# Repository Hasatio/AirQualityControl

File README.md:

# Air Quality Control

The circuit taken as an example while designing the board [Sparkfun BME688](https://www.sparkfun.com/products/19096)

## Revision 0

### Added:

- 1x TCA9406 (Voltage Level Translator)
- 1x PCA9554 (I/O Expander)
- 8x Relay
- 1x K7805-2000R3L or K7805-2000R3 for 5V supply

### Changed:

- Logo

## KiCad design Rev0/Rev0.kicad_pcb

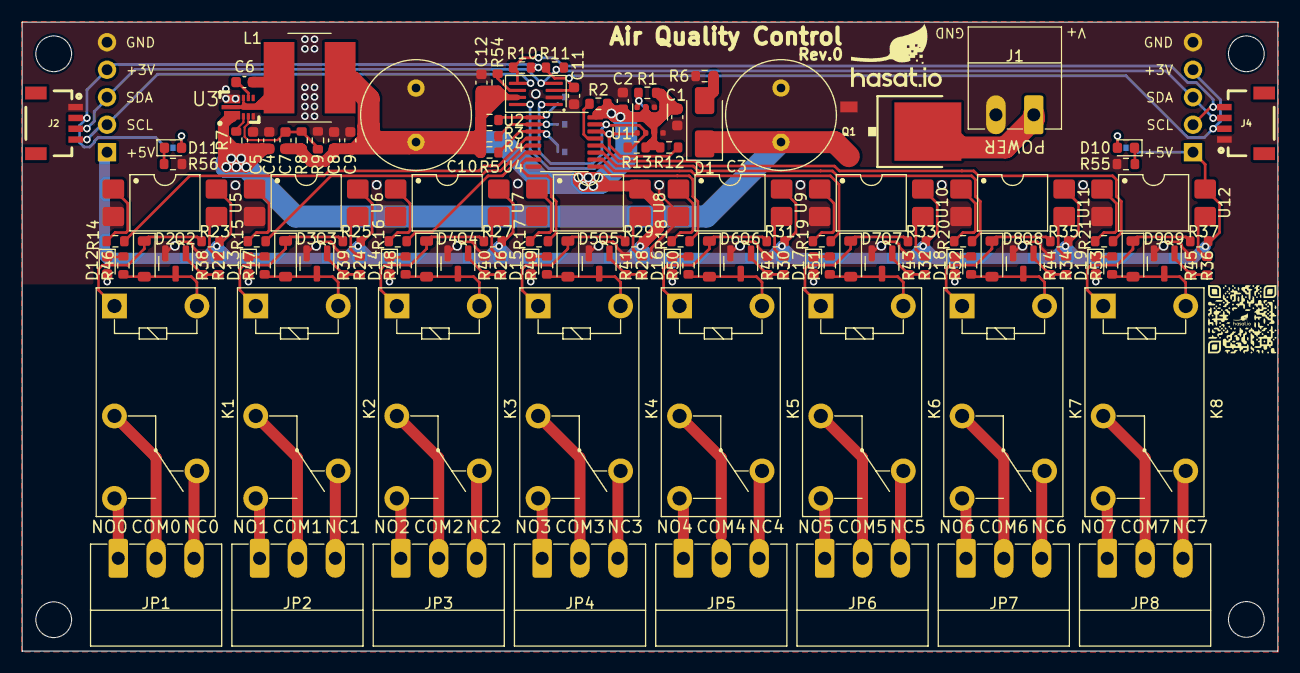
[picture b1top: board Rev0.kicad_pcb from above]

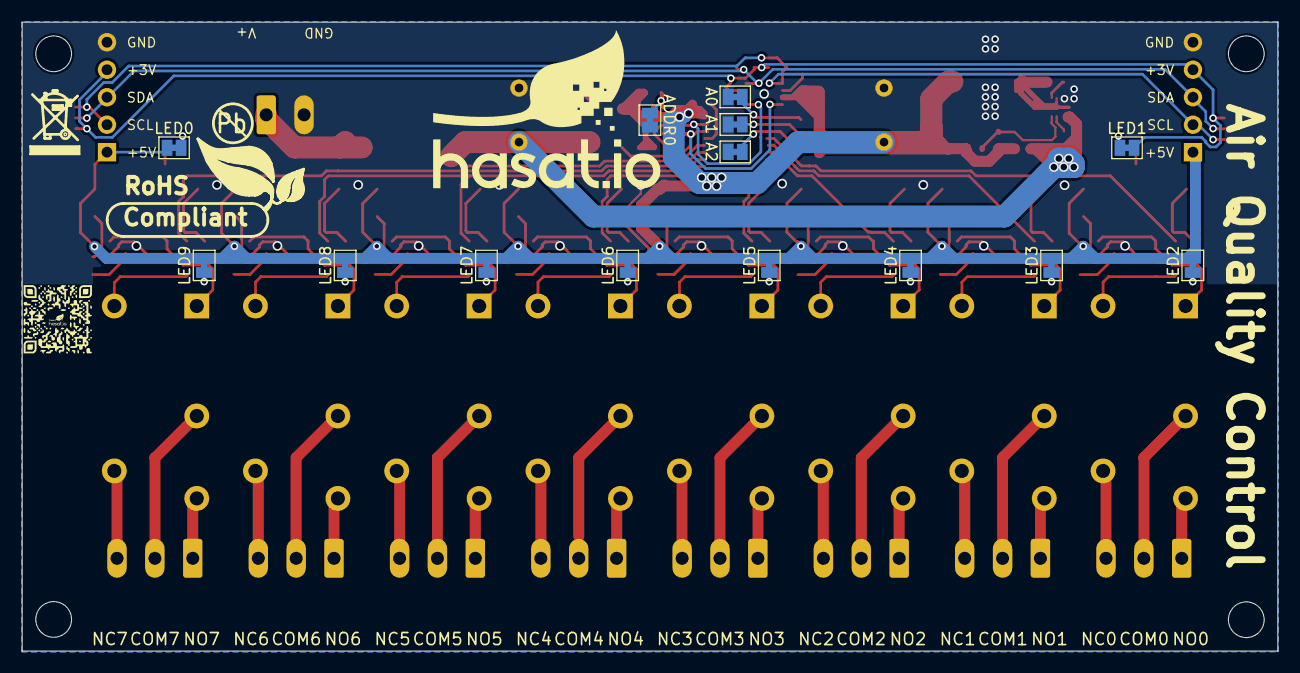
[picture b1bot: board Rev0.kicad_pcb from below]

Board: 2 copper layers, 116.0 x 58.1 mm, 147 parts (17 on the bottom side), 112 nets.

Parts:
A0, A1, A2: SolderJumper_2_Bridged; SolderJumper-2_P1.3mm_Bridged_Pad1.0x1.5mm
ADDR0: SolderJumper_2_Bridged; SolderJumper-2_P1.3mm_Bridged_Pad1.0x1.5mm
C1, C2, C6, C11, C12: 0.1uF; C_0603_1608Metric
C3, C10: 1000uF/35v; C_Radial_D10.0mm_H20.0mm_P5.00mm
C4, C5: 4.7uF-50V; C_0603_1608Metric
C7: 47pF-5%-X7R; C_0603_1608Metric
C8, C9: 22uF; C_0603_1608Metric
D1: Z1SMA4740; D_SMA
D2, D3, D4, D5, D6, D7, D8, D9: 1N4148W; D_SOD-123
D10: GREEN; LED_0603_1608Metric
D11: RED; LED_0603_1608Metric
D12, D13, D14, D15, D16, D17, D18, D19: BLUE; LED_0603_1608Metric
J1: TERMBLOCK_1X2; PhoenixContact_MC_1,5_2-G-3.5_1x02_P3.50mm_Horizontal
J2, J4: QWIIC_RIGHT_ANGLE; 1X04_1MM_RA_STRESSRELIEF
J3, J5: Conn_01x05; PinHeader_1x05_P2.54mm_Vertical
JP1, JP2, JP3, JP4, JP5, JP6, JP7, JP8: HEADER-1X3_508TERM; PhoenixContact_MC_1,5_3-G-3.5_1x03_P3.50mm_Horizontal
K1, K2, K3, K4, K5, K6, K7, K8: G5Q-1; Relay_SPDT_Omron-G5Q-1
L1: 6.8uH; L_Bourns_SRN8040TA
LED0, LED1, LED2, LED3, LED4, LED5, LED6, LED7, LED8, LED9: SolderJumper_2_Bridged; SolderJumper-2_P1.3mm_Bridged_Pad1.0x1.5mm
Q1: AOD417; TO252
Q2, Q3, Q4, Q5, Q6, Q7, Q8, Q9: MMBT2222; SOT-23
R1, R2, R3, R4, R5, R10, R11, R12, R13, R38, R39, R40, R41, R42, R43, R44, R45, R54: 10K; R_0603_1608Metric
R6: 100k; R_0603_1608Metric
R7: 10k; R_0603_1608Metric
R8: 158k; R_0603_1608Metric
R9: 30k; R_0603_1608Metric
R14, R15, R16, R17, R18, R19, R20, R21: 360R; R_0603_1608Metric
R22, R24, R26, R28, R30, R32, R34, R36: 330R; R_0603_1608Metric
R23, R25, R27, R29, R31, R33, R35, R37: 10R; R_0603_1608Metric
R46, R47, R48, R49, R50, R51, R52, R53: 1K; R_0603_1608Metric
R55: 2k2; R_0603_1608Metric
R56: 1k; R_0603_1608Metric
Sign-RecyclBin: LOGO_RECYCLEBIN_1
Sign_Pb-Free: LOGO_PBFREE
Sign_RoHS: Val**; LOGO_ROHS_1
U1: BME688; Bosch_LGA-8_3x3mm_P0.8mm_ClockwisePinNumbering
U2: TCA9406DC; SSOP-8_2.95x2.8mm_P0.65mm
U3: AP63357; V-DFN3020-13
U4: TCA9534A; TSSOP-16_4.4x5mm_P0.65mm
U5, U6, U7, U8, U9, U10, U11, U12: LTV-817S; SMDIP-4_W9.53mm

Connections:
+3.3V: C11.1, J2.2, J3.4, J4.2, J5.4, LED1.1 (A), R10.1, R11.1, U2.3 (VCCA)
+5V: C1.1, C2.1, C7.1, C8.1, C9.1, C10.1, C12.1, J3.1, J5.1, L1.2, LED0.1 (A), LED2.1 (A), LED3.1 (A), LED4.1 (A), LED5.1 (A), LED6.1 (A), LED7.1 (A), LED8.1 (A), LED9.1 (A), R1.2, R2.2, R3.2, R4.2, R5.2, R8.2, R12.1, R13.1, R23.1, R25.1, R27.1, R29.1, R31.1, R33.1, R35.1, R37.1, R54.1, U1.2 (CSB), U1.6 (VDDIO), U1.8 (VDD), U2.7 (VCCB), U4.16 (VDD), U5.4, U6.4, U7.4, U8.4, U9.4, U10.4, U11.4, U12.4
/A0: A0.1 (A), R3.1, U4.1 (A0)
/A1: A1.1 (A), R4.1, U4.2 (A1)
/A2: A2.1 (A), R5.1, U4.3 (A2)
/COM0: JP1.2, K1.2
/COM1: JP2.2, K2.2
/COM2: JP3.2, K3.2
/COM3: JP4.2, K4.2
/COM4: JP5.2, K5.2
/COM5: JP6.2, K6.2
/COM6: JP7.2, K7.2
/COM7: JP8.2, K8.2
/NC0: JP1.3, K1.4
/NC1: JP2.3, K2.4
/NC2: JP3.3, K3.4
/NC3: JP4.3, K4.4
/NC4: JP5.3, K5.4
/NC5: JP6.3, K6.4
/NC6: JP7.3, K7.4
/NC7: JP8.3, K8.4
/NO0: JP1.1, K1.3
/NO1: JP2.1, K2.3
/NO2: JP3.1, K3.3
/NO3: JP4.1, K4.3
/NO4: JP5.1, K5.3
/NO5: JP6.1, K6.3
/NO6: JP7.1, K7.3
/NO7: JP8.1, K8.3
/Out0: R14.2, U4.4 (P0)
/Out1: R15.2, U4.5 (P1)
/Out2: R16.2, U4.6 (P2)
/Out3: R17.2, U4.7 (P3)
/Out4: R18.2, U4.9 (P4)
/Out5: R19.2, U4.10 (P5)
/Out6: R20.2, U4.11 (P6)
/Out7: R21.2, U4.12 (P7)
/Relay0: R22.2, U5.3
/Relay1: R24.1, U6.3
/Relay2: R26.1, U7.3
/Relay3: R28.1, U8.3
/Relay4: R30.1, U9.3
/Relay5: R32.1, U10.3
/Relay6: R34.1, U11.3
/Relay7: R36.1, U12.3
/SCL_A: J2.4, J3.2, J4.4, J5.2, R10.2, U2.5 (SCL_A)
/SCL_B: R12.2, U1.4 (SCK), U2.8 (SCL_B), U4.14 (SCL)
/SDA_A: J2.3, J3.3, J4.3, J5.3, R11.2, U2.4 (SDA_A)
/SDA_B: R13.2, U1.3 (SDI), U2.1 (SDA_B), U4.15 (SDA)
/SDO: ADDR0.1 (A), R1.1, U1.5 (SDO)
GND: A0.2 (B), A1.2 (B), A2.2 (B), ADDR0.2 (B), C1.2, C2.2, C3.2, C4.2, C5.2, C8.2, C9.2, C10.2, C11.2, C12.2, J1.2, J2.1, J3.5, J4.1, J5.5, Q1.1 (G), Q2.2 (E), Q3.2 (E), Q4.2 (E), Q5.2 (E), Q6.2 (E), Q7.2 (E), Q8.2 (E), Q9.2 (E), R6.1, R9.1, R38.1, R39.1, R40.1, R41.1, R42.1, R43.1, R44.1, R45.1, R55.2, R56.2, U1.1 (GND), U1.7 (GND), U2.2 (GND), U3.P$4 (COMP), U3.P$8 (GND), U4.8 (GND), U5.2, U6.2, U7.2, U8.2, U9.2, U10.2, U11.2, U12.2
unnamed: C6.2, L1.1, U3.P$7 (SW), U3.P$9 (SW)
unnamed: D1.2 (A), R6.2
unnamed: D2.2 (A), K1.5, Q2.3 (C), R46.1
unnamed: D2.1 (K), K1.1, R23.2
unnamed: D3.2 (A), K2.5, Q3.3 (C), R47.1
unnamed: D3.1 (K), K2.1, R25.2
unnamed: D4.2 (A), K3.5, Q4.3 (C), R48.1
unnamed: D4.1 (K), K3.1, R27.2
unnamed: D5.2 (A), K4.5, Q5.3 (C), R49.1
unnamed: D5.1 (K), K4.1, R29.2
unnamed: D6.2 (A), K5.5, Q6.3 (C), R50.1
unnamed: D6.1 (K), K5.1, R31.2
unnamed: D7.2 (A), K6.5, Q7.3 (C), R51.1
unnamed: D7.1 (K), K6.1, R33.2
unnamed: D8.2 (A), K7.5, Q8.3 (C), R52.1
unnamed: D8.1 (K), K7.1, R35.2
unnamed: D9.2 (A), K8.5, Q9.3 (C), R53.1
unnamed: D9.1 (K), K8.1, R37.2
unnamed: D10.2 (A), LED0.2 (B)
unnamed: D10.1 (K), R55.1
unnamed: D11.2 (A), LED1.2 (B)
unnamed: D11.1 (K), R56.1
unnamed: D12.2 (A), LED2.2 (B)
unnamed: D12.1 (K), R46.2
unnamed: D13.2 (A), LED3.2 (B)
unnamed: D13.1 (K), R47.2
unnamed: D14.2 (A), LED4.2 (B)
unnamed: D14.1 (K), R48.2
unnamed: D15.2 (A), LED5.2 (B)
unnamed: D15.1 (K), R49.2
unnamed: D16.2 (A), LED6.2 (B)
unnamed: D16.1 (K), R50.2
unnamed: D17.2 (A), LED7.2 (B)
unnamed: D17.1 (K), R51.2
unnamed: D18.2 (A), LED8.2 (B)
unnamed: D18.1 (K), R52.2
unnamed: D19.2 (A), LED9.2 (B)
unnamed: D19.1 (K), R53.2
unnamed: J1.1, Q1.3 (D)
unnamed: Q2.1 (B), R22.1, R38.2
unnamed: Q3.1 (B), R24.2, R39.2
unnamed: Q4.1 (B), R26.2, R40.2
unnamed: Q5.1 (B), R28.2, R41.2
unnamed: Q6.1 (B), R30.2, R42.2
unnamed: Q7.1 (B), R32.2, R43.2
unnamed: Q8.1 (B), R34.2, R44.2
unnamed: Q9.1 (B), R36.2, R45.2
unnamed: R14.1, U5.1
unnamed: R15.1, U6.1
unnamed: R16.1, U7.1
unnamed: R17.1, U8.1
unnamed: R18.1, U9.1
unnamed: R19.1, U10.1
unnamed: R20.1, U11.1
unnamed: R21.1, U12.1
unnamed: R54.2, U2.6 (OE)
unnamed: C6.1, U3.P$6 (BST)
unnamed: R7.1, U3.P$2 (EN)
unnamed: C7.2, R8.1, R9.2, U3.P$3 (FB)
unnamed: R2.1, U4.13 (~INT)
VCC: C3.1, C4.1, C5.1, D1.1 (K), Q1.2 (S), R7.2, U3.P$1 (VIN)

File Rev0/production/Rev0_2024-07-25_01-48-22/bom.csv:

Designator,Footprint,Quantity,Value,LCSC Part #
"A0, A1, A2, ADDR0, LED0, LED1, LED2, LED3, LED4, LED5, LED6, LED7, LED8, LED9",SolderJumper-2_P1.3mm_Bridged_Pad1.0x1.5mm,14,SolderJumper_2_Bridged,
"C1, C2, C7, C8",0603,4,0.1uF,
"C3, C6",C_Radial_D10.0mm_H20.0mm_P5.00mm,2,1000uF/35v,
C4,0805,1,10uF/100v,
C5,0603,1,10uF,
D1,0603,1,GREEN,
"D10, D11, D4, D5, D6, D7, D8, D9",D_SOD-123,8,1N4148W,
"D12, D13, D14, D15, D16, D17, D18, D19",0603,8,BLUE,
D2,0603,1,RED,
D3,D_SMA,1,Z1SMA4740,
FRAME1,CREATIVE_COMMONS,1,FRAME-LETTER,
J1,"PhoenixContact_MC_1,5_2-G-3.5_1x02_P3.50mm_Horizontal",1,TERMBLOCK_1X2,
"J2, J4",1X04_1MM_RA_STRESSRELIEF,2,QWIIC_RIGHT_ANGLE,
"J3, J5",PinHeader_1x05_P2.54mm_Vertical,2,Conn_01x05,
"JP10, JP11, JP12, JP13, JP14, JP15, JP16, JP9","PhoenixContact_MC_1,5_3-G-3.5_1x03_P3.50mm_Horizontal",8,HEADER-1X3_508TERM,
"JP3, JP4, JP7, JP8",STAND-OFF,4,STAND-OFF,
"K1, K2, K3, K4, K5, K6, K7, K8",Relay_SPDT_Omron-G5Q-1,8,G5Q-1,
Q1,TO252,1,AOD417,
"Q2, Q3, Q4, Q5, Q6, Q7, Q8, Q9",SOT-23,8,MMBT2222,
"R1, R10, R2, R3, R38, R39, R4, R40, R41, R42, R43, R44, R45, R5, R6, R7, R8, R9",0603,18,10K,
R11,0603,1,100k,
R12,0603,1,2k2,
"R13, R46, R47, R48, R49, R50, R51, R52, R53",0603,9,1k,
"R14, R15, R16, R17, R18, R19, R20, R21",0603,8,380R,
"R22, R24, R26, R28, R30, R32, R34, R36",0603,8,330R,
"R23, R25, R27, R29, R31, R33, R35, R37",0603,8,10,
Sign-RecyclBin,LOGO_RECYCLEBIN_1,1,,
Sign_Pb-Free,LOGO_PBFREE,1,,
Sign_RoHS,LOGO_ROHS_1,1,Val**,
U1,Bosch_LGA-8_3x3mm_P0.8mm_ClockwisePinNumbering,1,BME688,
"U10, U11, U12, U5, U6, U7, U8, U9",SMDIP-4_W9.53mm,8,LTV-817S,
U2,SSOP-8_2.95x2.8mm_P0.65mm,1,TCA9406DC,
U3,Converter_DCDC_RECOM_R-78HB-0.5L_THT,1,K7805-2000R3L,
U4,TSSOP-16_4.4x5mm_P0.65mm,1,TCA9554,

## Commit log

2024-07-23 start
